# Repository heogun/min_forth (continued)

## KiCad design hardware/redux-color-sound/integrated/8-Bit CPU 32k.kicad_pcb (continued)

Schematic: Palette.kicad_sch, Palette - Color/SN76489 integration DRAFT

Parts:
R28, R29: 750; R_Axial_DIN0207_L6.3mm_D2.5mm_P7.62mm_Horizontal
R30, R31, R32: 1.5k; R_Axial_DIN0207_L6.3mm_D2.5mm_P7.62mm_Horizontal
U83: 74HC173; DIP-16_W7.62mm_Socket
U84: 74HC08; DIP-14_W7.62mm_Socket
U85, U86: 74HC4002; DIP-14_W7.62mm_Socket
U87: 74HC30; DIP-14_W7.62mm_Socket
U88, U89: 74HC157; DIP-16_W7.62mm_Socket
U90: 74AC244; DIP-20_W7.62mm_Socket

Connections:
16MHz: U83.7 (Cp); also elsewhere on the board
+5V: U83.16 (VCC), U84.14 (VCC), U85.14 (VDD), U86.14 (VDD), U87.6, U87.11, U87.12, U87.14 (VCC), U88.16 (VCC), U89.16 (VCC), U90.20 (VCC); also elsewhere on the board
CS_ACTIVE: U83.14 (D0), U86.13
CS_ACTIVE_LATCH: U83.3 (Q0); also elsewhere on the board
CS_ATTR_Q0: U88.3 (I1a); also elsewhere on the board
CS_ATTR_Q1: U88.6 (I1b); also elsewhere on the board
CS_ATTR_Q2: U88.10 (I1c); also elsewhere on the board
CS_ATTR_Q3: U88.13 (I1d); also elsewhere on the board
CS_ATTR_Q4: U88.2 (I0a); also elsewhere on the board
CS_ATTR_Q5: U88.5 (I0b); also elsewhere on the board
CS_ATTR_Q6: U88.11 (I0c); also elsewhere on the board
CS_ATTR_Q7: U88.14 (I0d); also elsewhere on the board
CS_B: U89.4 (Za), U90.11 (I0b)
CS_CA7: U85.2; also elsewhere on the board
CS_CA8: U85.3; also elsewhere on the board
CS_CA9: U85.4; also elsewhere on the board
CS_CA10: U85.5; also elsewhere on the board
CS_COLOR0: U88.4 (Za), U89.3 (I1a)
CS_COLOR1: U88.7 (Zb), U89.6 (I1b)
CS_COLOR2: U88.9 (Zc), U89.10 (I1c)
CS_COLOR3: U88.12 (Zd), U89.13 (I1d)
CS_COLOR_EN: U83.13 (D1); also elsewhere on the board
CS_COLOR_LATCH: U83.4 (Q1), U89.1 (S)
CS_DAC_B: R29.1, U90.9 (O0b)
CS_DAC_BI: R32.1, U90.7 (O1b)
CS_DAC_G: R28.1, U90.14 (O2a)
CS_DAC_GI: R31.1, U90.12 (O3a)
CS_DAC_R: U90.18 (O0a); also elsewhere on the board
CS_DAC_RI: R30.1, U90.16 (O1a)
CS_G: U89.7 (Zb), U90.6 (I2a)
CS_H12: U84.3, U85.11
CS_HHIGH_BAD: U86.1, U86.11
CS_HHIGH_OK: U86.2, U86.3, U86.4, U86.5, U87.8
CS_HLOW: U85.13, U86.10
CS_I: U89.12 (Zd), U90.4 (I1a), U90.8 (I3a), U90.13 (I1b)
CS_PIXEL: U88.1 (S), U89.2 (I0a), U89.5 (I0b), U89.11 (I0c), U89.14 (I0d); also elsewhere on the board
CS_R: U89.9 (Zc), U90.2 (I0a)
CS_RESET: U83.15 (Mr); also elsewhere on the board
CS_RGB_BLANK: U90.1 (OEa), U90.19 (OEb); also elsewhere on the board
CS_V256: U86.12; also elsewhere on the board
CS_VA1: U87.5; also elsewhere on the board
CS_VA2: U84.2, U87.4; also elsewhere on the board
CS_VA3: U84.1, U87.3; also elsewhere on the board
CS_VA4: U85.10, U87.2; also elsewhere on the board
CS_VA5: U85.9, U87.1; also elsewhere on the board
CS_VBAD: U85.1, U86.9
CS_VGA_B: R29.2, R32.2; also elsewhere on the board
CS_VGA_G: R28.2, R31.2; also elsewhere on the board
CS_VGA_R: R30.2; also elsewhere on the board
GND: U83.1 (Oe1), U83.2 (Oe2), U83.8 (GND), U83.10 (E2), U83.11 (D3), U83.12 (D2), U84.4, U84.5, U84.7 (GND), U84.9, U84.10, U84.12, U84.13, U85.7 (VSS), U85.12, U86.7 (VSS), U87.7 (GND), U88.8 (GND), U88.15 (E), U89.8 (GND), U89.15 (E), U90.10 (GND), U90.15 (I2b), U90.17 (I3b); also elsewhere on the board
~VGA_GET: U83.9 (E1); also elsewhere on the board

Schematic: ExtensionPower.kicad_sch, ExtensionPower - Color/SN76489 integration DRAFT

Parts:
C34, C35, C36, C37, C38, C39, C40, C41, C42, C44, C45, C46, C47, C48, C49, C50, C51, C52, C53, C54, C55, C56, C57, C58, C59, C60, C63: 100n; C_Disc_D5.0mm_W2.5mm_P2.50mm
C61: 10u 16V; CP_Radial_D5.0mm_P2.50mm

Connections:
+5V: C34.1, C35.1, C36.1, C37.1, C38.1, C39.1, C40.1, C41.1, C42.1, C44.1, C45.1, C46.1, C47.1, C48.1, C49.1, C50.1, C51.1, C52.1, C53.1, C54.1, C55.1, C56.1, C57.1, C58.1, C59.1, C60.1, C61.1, C63.1; also elsewhere on the board
GND: C34.2, C35.2, C36.2, C37.2, C38.2, C39.2, C40.2, C41.2, C42.2, C44.2, C45.2, C46.2, C47.2, C48.2, C49.2, C50.2, C51.2, C52.2, C53.2, C54.2, C55.2, C56.2, C57.2, C58.2, C59.2, C60.2, C61.2, C63.2; also elsewhere on the board

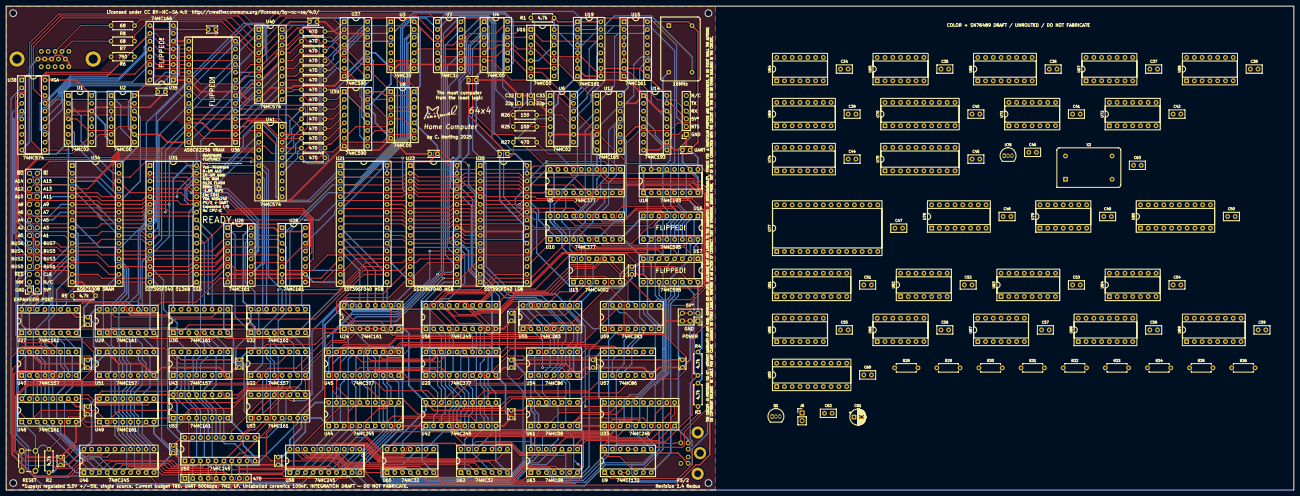
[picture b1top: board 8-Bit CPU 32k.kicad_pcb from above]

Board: 2 copper layers, 420.8 x 158.1 mm, 189 parts (0 on the bottom side), 349 nets.

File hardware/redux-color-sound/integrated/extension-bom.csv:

Reference,Value,Footprint,Schematic sheet
U64,74HC30,Package_DIP:DIP-14_W7.62mm_Socket,ExtensionIO
U65,74HC04,Package_DIP:DIP-14_W7.62mm_Socket,ExtensionIO
U66,74HC138,Package_DIP:DIP-16_W7.62mm_Socket,ExtensionIO
U67,74HC11,Package_DIP:DIP-14_W7.62mm_Socket,ExtensionIO
U68,74HC11,Package_DIP:DIP-14_W7.62mm_Socket,ExtensionIO
U69,74HC173,Package_DIP:DIP-16_W7.62mm_Socket,ExtensionIO
U70,74HC377,Package_DIP:DIP-20_W7.62mm_Socket,ExtensionIO
U71,74HC32,Package_DIP:DIP-14_W7.62mm_Socket,ExtensionIO
U72,74HC32,Package_DIP:DIP-14_W7.62mm_Socket,ExtensionIO
U74,SN76489AN,Package_DIP:DIP-16_W7.62mm_Socket,PSG
U75,74HCT244,Package_DIP:DIP-20_W7.62mm_Socket,PSG
U76,MCP130-450DI/TO,Package_TO_SOT_THT:TO-92_Inline,PSG
X2,3.579545MHz 5V FULL,Oscillator:Oscillator_DIP-14,PSG
U77,AS6C62256-55PCN ATTRIBUTE,Package_DIP:DIP-28_W15.24mm_Socket,Attribute
U78,74HC283,Package_DIP:DIP-16_W7.62mm_Socket,Attribute
U79,74HC86,Package_DIP:DIP-14_W7.62mm_Socket,Attribute
U80,74HC245,Package_DIP:DIP-20_W7.62mm_Socket,Attribute
U81,74HCT377,Package_DIP:DIP-20_W7.62mm_Socket,Attribute
U82,74HC74,Package_DIP:DIP-14_W7.62mm_Socket,Attribute
U83,74HC173,Package_DIP:DIP-16_W7.62mm_Socket,Palette
U84,74HC08,Package_DIP:DIP-14_W7.62mm_Socket,Palette
U85,74HC4002,Package_DIP:DIP-14_W7.62mm_Socket,Palette
U86,74HC4002,Package_DIP:DIP-14_W7.62mm_Socket,Palette
U87,74HC30,Package_DIP:DIP-14_W7.62mm_Socket,Palette
U88,74HC157,Package_DIP:DIP-16_W7.62mm_Socket,Palette
U89,74HC157,Package_DIP:DIP-16_W7.62mm_Socket,Palette
U90,74AC244,Package_DIP:DIP-20_W7.62mm_Socket,Palette
R28,750,Resistor_THT:R_Axial_DIN0207_L6.3mm_D2.5mm_P7.62mm_Horizontal,Palette
R29,750,Resistor_THT:R_Axial_DIN0207_L6.3mm_D2.5mm_P7.62mm_Horizontal,Palette
R30,1.5k,Resistor_THT:R_Axial_DIN0207_L6.3mm_D2.5mm_P7.62mm_Horizontal,Palette
R31,1.5k,Resistor_THT:R_Axial_DIN0207_L6.3mm_D2.5mm_P7.62mm_Horizontal,Palette
R32,1.5k,Resistor_THT:R_Axial_DIN0207_L6.3mm_D2.5mm_P7.62mm_Horizontal,Palette
R33,4.7k,Resistor_THT:R_Axial_DIN0207_L6.3mm_D2.5mm_P7.62mm_Horizontal,PSG
R34,1k,Resistor_THT:R_Axial_DIN0207_L6.3mm_D2.5mm_P7.62mm_Horizontal,PSG
R35,10k,Resistor_THT:R_Axial_DIN0207_L6.3mm_D2.5mm_P7.62mm_Horizontal,PSG
R36,100k,Resistor_THT:R_Axial_DIN0207_L6.3mm_D2.5mm_P7.62mm_Horizontal,PSG
Q1,2N7000,Package_TO_SOT_THT:TO-92_Inline,PSG
J6,MONO LINE OUT / EXTERNAL AMP,Connector_PinHeader_2.54mm:PinHeader_1x02_P2.54mm_Vertical,PSG
C62,220n,Capacitor_THT:C_Disc_D5.0mm_W2.5mm_P2.50mm,PSG
C34,100n,Capacitor_THT:C_Disc_D5.0mm_W2.5mm_P2.50mm,ExtensionPower
C35,100n,Capacitor_THT:C_Disc_D5.0mm_W2.5mm_P2.50mm,ExtensionPower
C36,100n,Capacitor_THT:C_Disc_D5.0mm_W2.5mm_P2.50mm,ExtensionPower
C37,100n,Capacitor_THT:C_Disc_D5.0mm_W2.5mm_P2.50mm,ExtensionPower
C38,100n,Capacitor_THT:C_Disc_D5.0mm_W2.5mm_P2.50mm,ExtensionPower
C39,100n,Capacitor_THT:C_Disc_D5.0mm_W2.5mm_P2.50mm,ExtensionPower
C40,100n,Capacitor_THT:C_Disc_D5.0mm_W2.5mm_P2.50mm,ExtensionPower
C41,100n,Capacitor_THT:C_Disc_D5.0mm_W2.5mm_P2.50mm,ExtensionPower
C42,100n,Capacitor_THT:C_Disc_D5.0mm_W2.5mm_P2.50mm,ExtensionPower
C44,100n,Capacitor_THT:C_Disc_D5.0mm_W2.5mm_P2.50mm,ExtensionPower
C45,100n,Capacitor_THT:C_Disc_D5.0mm_W2.5mm_P2.50mm,ExtensionPower
C46,100n,Capacitor_THT:C_Disc_D5.0mm_W2.5mm_P2.50mm,ExtensionPower
C47,100n,Capacitor_THT:C_Disc_D5.0mm_W2.5mm_P2.50mm,ExtensionPower
C48,100n,Capacitor_THT:C_Disc_D5.0mm_W2.5mm_P2.50mm,ExtensionPower
C49,100n,Capacitor_THT:C_Disc_D5.0mm_W2.5mm_P2.50mm,ExtensionPower
C50,100n,Capacitor_THT:C_Disc_D5.0mm_W2.5mm_P2.50mm,ExtensionPower
C51,100n,Capacitor_THT:C_Disc_D5.0mm_W2.5mm_P2.50mm,ExtensionPower
C52,100n,Capacitor_THT:C_Disc_D5.0mm_W2.5mm_P2.50mm,ExtensionPower
C53,100n,Capacitor_THT:C_Disc_D5.0mm_W2.5mm_P2.50mm,ExtensionPower
C54,100n,Capacitor_THT:C_Disc_D5.0mm_W2.5mm_P2.50mm,ExtensionPower
C55,100n,Capacitor_THT:C_Disc_D5.0mm_W2.5mm_P2.50mm,ExtensionPower
C56,100n,Capacitor_THT:C_Disc_D5.0mm_W2.5mm_P2.50mm,ExtensionPower
C57,100n,Capacitor_THT:C_Disc_D5.0mm_W2.5mm_P2.50mm,ExtensionPower
C58,100n,Capacitor_THT:C_Disc_D5.0mm_W2.5mm_P2.50mm,ExtensionPower
C59,100n,Capacitor_THT:C_Disc_D5.0mm_W2.5mm_P2.50mm,ExtensionPower
C60,100n,Capacitor_THT:C_Disc_D5.0mm_W2.5mm_P2.50mm,ExtensionPower
C61,10u 16V,Capacitor_THT:CP_Radial_D5.0mm_P2.50mm,ExtensionPower
C63,100n,Capacitor_THT:C_Disc_D5.0mm_W2.5mm_P2.50mm,ExtensionPower

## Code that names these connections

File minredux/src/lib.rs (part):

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pub const FI: u32 = 1 << 6;
pub const IO: u32 = 1 << 7;
pub const MC: u32 = 1 << 8;
pub const CIH: u32 = 1 << 9;
pub const CE: u32 = 1 << 10;
pub const BI: u32 = 1 << 11;
pub const AI: u32 = 1 << 12;
pub const AO: u32 = 1 << 13;
pub const COH: u32 = 1 << 14;
pub const COL: u32 = 1 << 15;
pub const MIL: u32 = 1 << 16;
pub const MIH: u32 = 1 << 17;
pub const ME: u32 = 1 << 18;
pub const CIL: u32 = 1 << 19;
pub const MZ: u32 = 1 << 20;
pub const RO: u32 = 1 << 21;
pub const NI: u32 = 1 << 22;
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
